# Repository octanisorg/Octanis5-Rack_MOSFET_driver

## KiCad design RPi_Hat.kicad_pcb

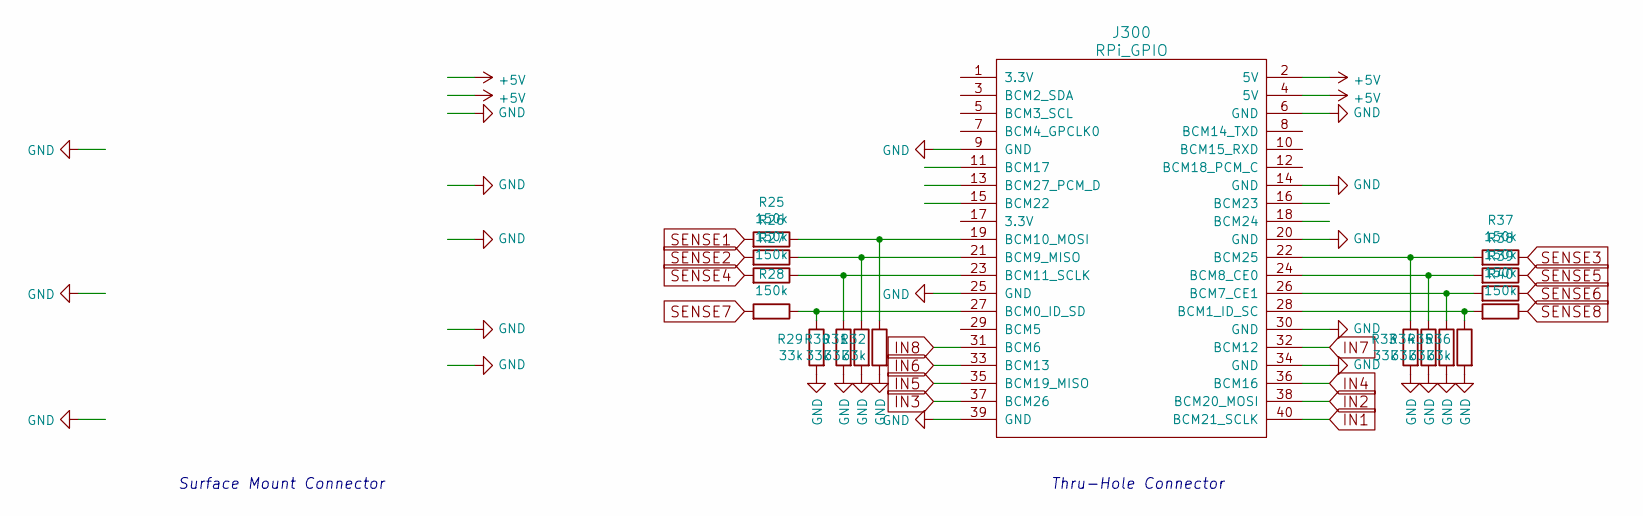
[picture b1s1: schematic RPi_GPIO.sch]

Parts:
J300: RPi_GPIO; Pin_Header_Straight_2x20; LCSC P/N C50982
R25, R26, R27, R28, R37, R38, R39, R40: 150k; R_0603; LCSC P/N C22807
R29, R30, R31, R32, R33, R34, R35, R36: 33k; R_0603; LCSC P/N C4216

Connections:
+5V: J300.2 (5V), J300.4 (5V); also elsewhere on the board
GND: J300.6 (GND), J300.9 (GND), J300.14 (GND), J300.20 (GND), J300.25 (GND), J300.30 (GND), J300.34 (GND), J300.39 (GND), R29.2, R30.2, R31.2, R32.2, R33.2, R34.2, R35.2, R36.2; also elsewhere on the board
IN1: J300.40 (BCM21_SCLK); also elsewhere on the board
IN2: J300.38 (BCM20_MOSI); also elsewhere on the board
IN3: J300.37 (BCM26); also elsewhere on the board
IN4: J300.36 (BCM16); also elsewhere on the board
IN5: J300.35 (BCM19_MISO); also elsewhere on the board
IN6: J300.33 (BCM13); also elsewhere on the board
IN7: J300.32 (BCM12); also elsewhere on the board
IN8: J300.31 (BCM6); also elsewhere on the board
unnamed: J300.19 (BCM10_MOSI), R25.1, R32.1
unnamed: J300.21 (BCM9_MISO), R26.1, R31.1
unnamed: J300.22 (BCM25), R33.1, R37.2
unnamed: J300.23 (BCM11_SCLK), R27.1, R30.1
unnamed: J300.24 (BCM8_CE0), R34.1, R38.2
unnamed: J300.26 (BCM7_CE1), R35.1, R39.2
unnamed: J300.27 (BCM0_ID_SD), R28.1, R29.1
unnamed: J300.28 (BCM1_ID_SC), R36.1, R40.2
SENSE1: R25.2; also elsewhere on the board
SENSE2: R26.2; also elsewhere on the board
SENSE3: R37.1; also elsewhere on the board
SENSE4: R27.2; also elsewhere on the board
SENSE5: R38.1; also elsewhere on the board
SENSE6: R39.1; also elsewhere on the board
SENSE7: R28.2; also elsewhere on the board
SENSE8: R40.1; also elsewhere on the board

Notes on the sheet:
Surface Mount Connector
Thru-Hole Connector

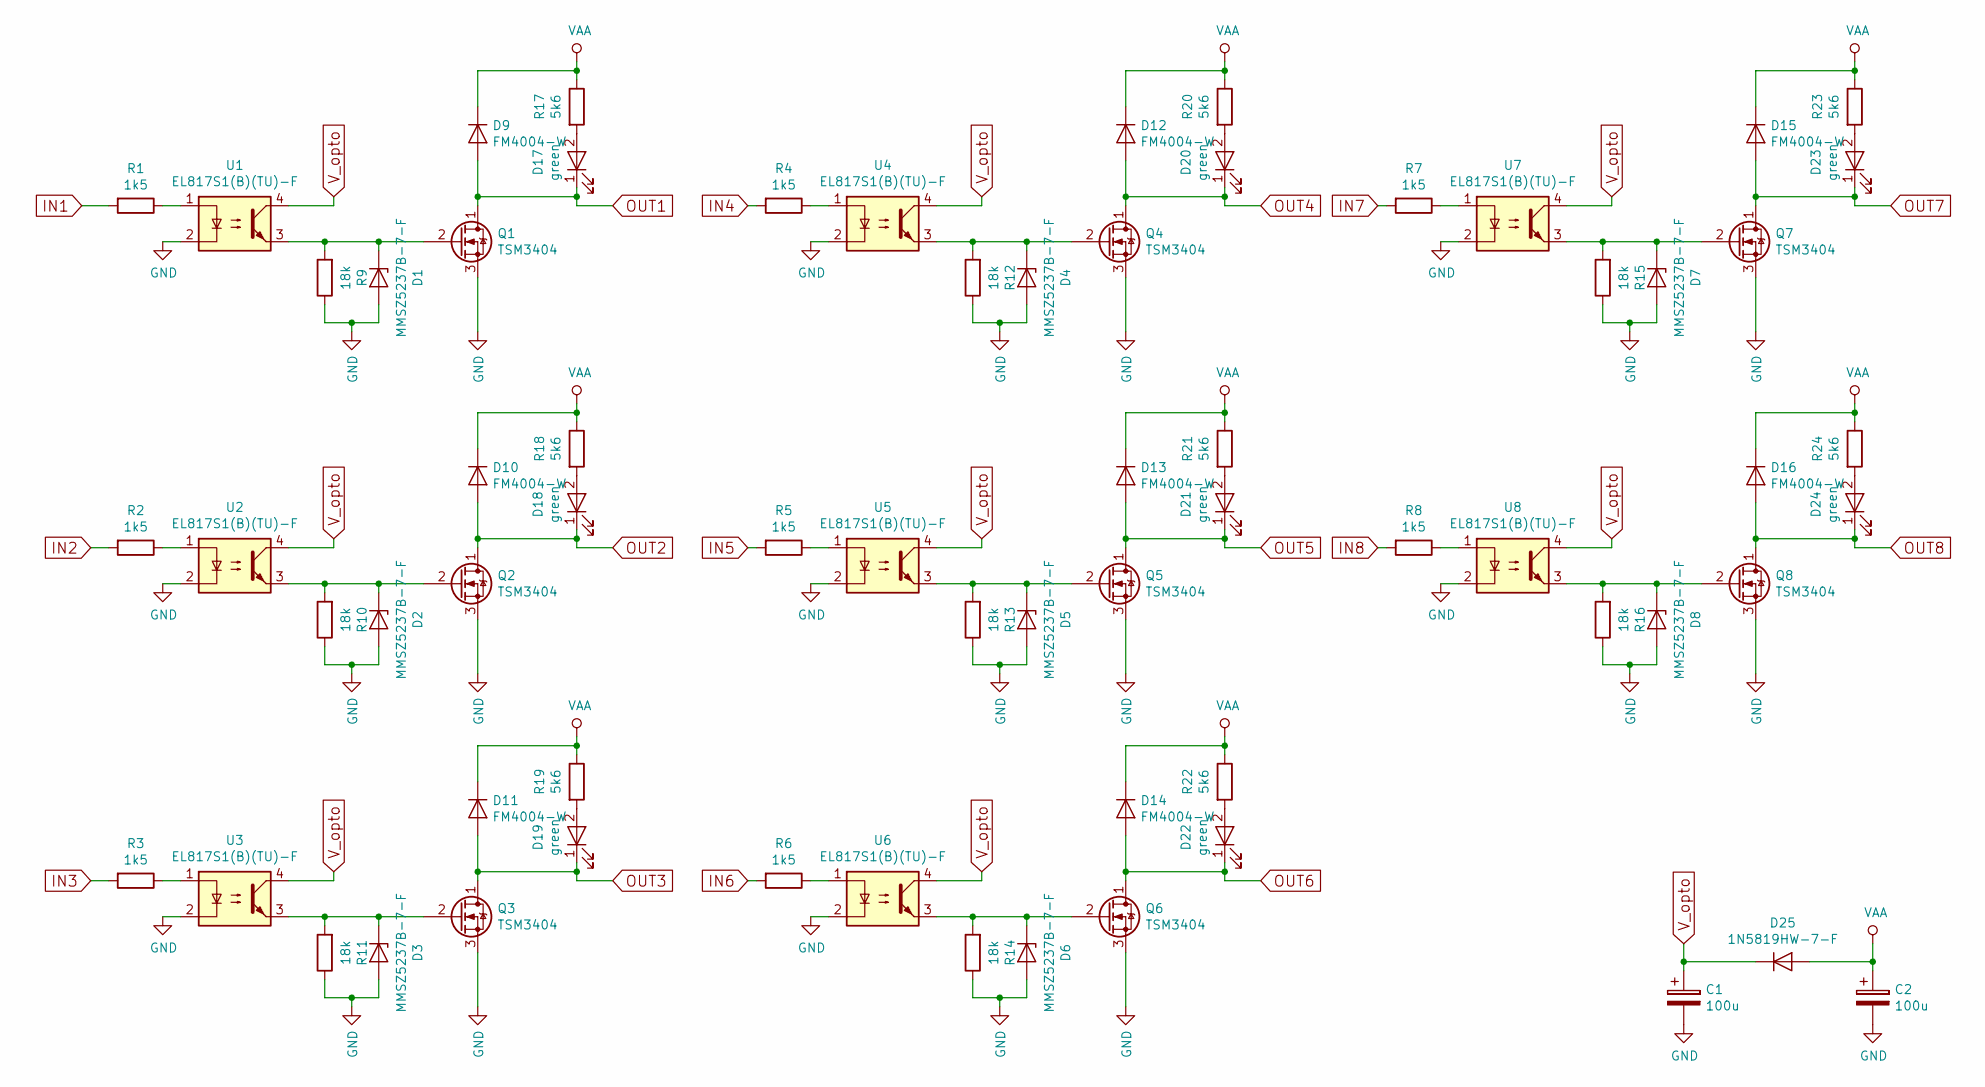
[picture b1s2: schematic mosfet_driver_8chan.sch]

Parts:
C1, C2: 100u; C_Radial_D8_L13_P3.8; LCSC P/N C45674
D1, D2, D3, D4, D5, D6, D7, D8: MMSZ5237B-7-F; SOD-123; LCSC P/N C65078
D9, D10, D11, D12, D13, D14, D15, D16: FM4004-W; SMB_Standard; LCSC P/N C122842
D17, D18, D19, D20, D21, D22, D23, D24: green; LED_0603; LCSC P/N C118334
D25: 1N5819HW-7-F; SOD-123; LCSC P/N C82544
Q1, Q2, Q3, Q4, Q5, Q6, Q7, Q8: TSM3404; SOT-23; LCSC P/N C71151
R1, R2, R3, R4, R5, R6, R7, R8: 1k5; R_0603; LCSC P/N C138275
R9, R10, R11, R12, R13, R14, R15, R16: 18k; R_0603; LCSC P/N C100821
R17, R18, R19, R20, R21, R22, R23, R24: 5k6; R_0603; LCSC P/N C101368
U1, U2, U3, U4, U5, U6, U7, U8: EL817S1(B)(TU)-F; EL817S1-B-TU-F; LCSC P/N C63268

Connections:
GND: C1.2, C2.2, D1.2 (A), D2.2 (A), D3.2 (A), D4.2 (A), D5.2 (A), D6.2 (A), D7.2 (A), D8.2 (A), Q1.3 (S), Q2.3 (S), Q3.3 (S), Q4.3 (S), Q5.3 (S), Q6.3 (S), Q7.3 (S), Q8.3 (S), R9.1, R10.1, R11.1, R12.1, R13.1, R14.1, R15.1, R16.1, U1.2, U2.2, U3.2, U4.2, U5.2, U6.2, U7.2, U8.2; also elsewhere on the board
IN1: R1.2; also elsewhere on the board
IN2: R2.2; also elsewhere on the board
IN3: R3.2; also elsewhere on the board
IN4: R4.2; also elsewhere on the board
IN5: R5.2; also elsewhere on the board
IN6: R6.2; also elsewhere on the board
IN7: R7.2; also elsewhere on the board
IN8: R8.2; also elsewhere on the board
unnamed: D1.1 (K), Q1.2 (G), R9.2, U1.3
unnamed: D2.1 (K), Q2.2 (G), R10.2, U2.3
unnamed: D3.1 (K), Q3.2 (G), R11.2, U3.3
unnamed: D4.1 (K), Q4.2 (G), R12.2, U4.3
unnamed: D5.1 (K), Q5.2 (G), R13.2, U5.3
unnamed: D6.1 (K), Q6.2 (G), R14.2, U6.3
unnamed: D7.1 (K), Q7.2 (G), R15.2, U7.3
unnamed: D8.1 (K), Q8.2 (G), R16.2, U8.3
unnamed: D17.2 (A), R17.2
unnamed: D18.2 (A), R18.2
unnamed: D19.2 (A), R19.2
unnamed: D20.2 (A), R20.2
unnamed: D21.2 (A), R21.2
unnamed: D22.2 (A), R22.2
unnamed: D23.2 (A), R23.2
unnamed: D24.2 (A), R24.2
unnamed: R1.1, U1.1
unnamed: R2.1, U2.1
unnamed: R3.1, U3.1
unnamed: R4.1, U4.1
unnamed: R5.1, U5.1
unnamed: R6.1, U6.1
unnamed: R7.1, U7.1
unnamed: R8.1, U8.1
OUT1: D9.2 (A), D17.1 (K), Q1.1 (D); also elsewhere on the board
OUT2: D10.2 (A), D18.1 (K), Q2.1 (D); also elsewhere on the board
OUT3: D11.2 (A), D19.1 (K), Q3.1 (D); also elsewhere on the board
OUT4: D12.2 (A), D20.1 (K), Q4.1 (D); also elsewhere on the board
OUT5: D13.2 (A), D21.1 (K), Q5.1 (D); also elsewhere on the board
OUT6: D14.2 (A), D22.1 (K), Q6.1 (D); also elsewhere on the board
OUT7: D15.2 (A), D23.1 (K), Q7.1 (D); also elsewhere on the board
OUT8: D16.2 (A), D24.1 (K), Q8.1 (D); also elsewhere on the board
VAA: C2.1, D9.1 (K), D10.1 (K), D11.1 (K), D12.1 (K), D13.1 (K), D14.1 (K), D15.1 (K), D16.1 (K), D25.2 (A), R17.1, R18.1, R19.1, R20.1, R21.1, R22.1, R23.1, R24.1; also elsewhere on the board
V_opto: C1.1, D25.1 (K), U1.4, U2.4, U3.4, U4.4, U5.4, U6.4, U7.4, U8.4

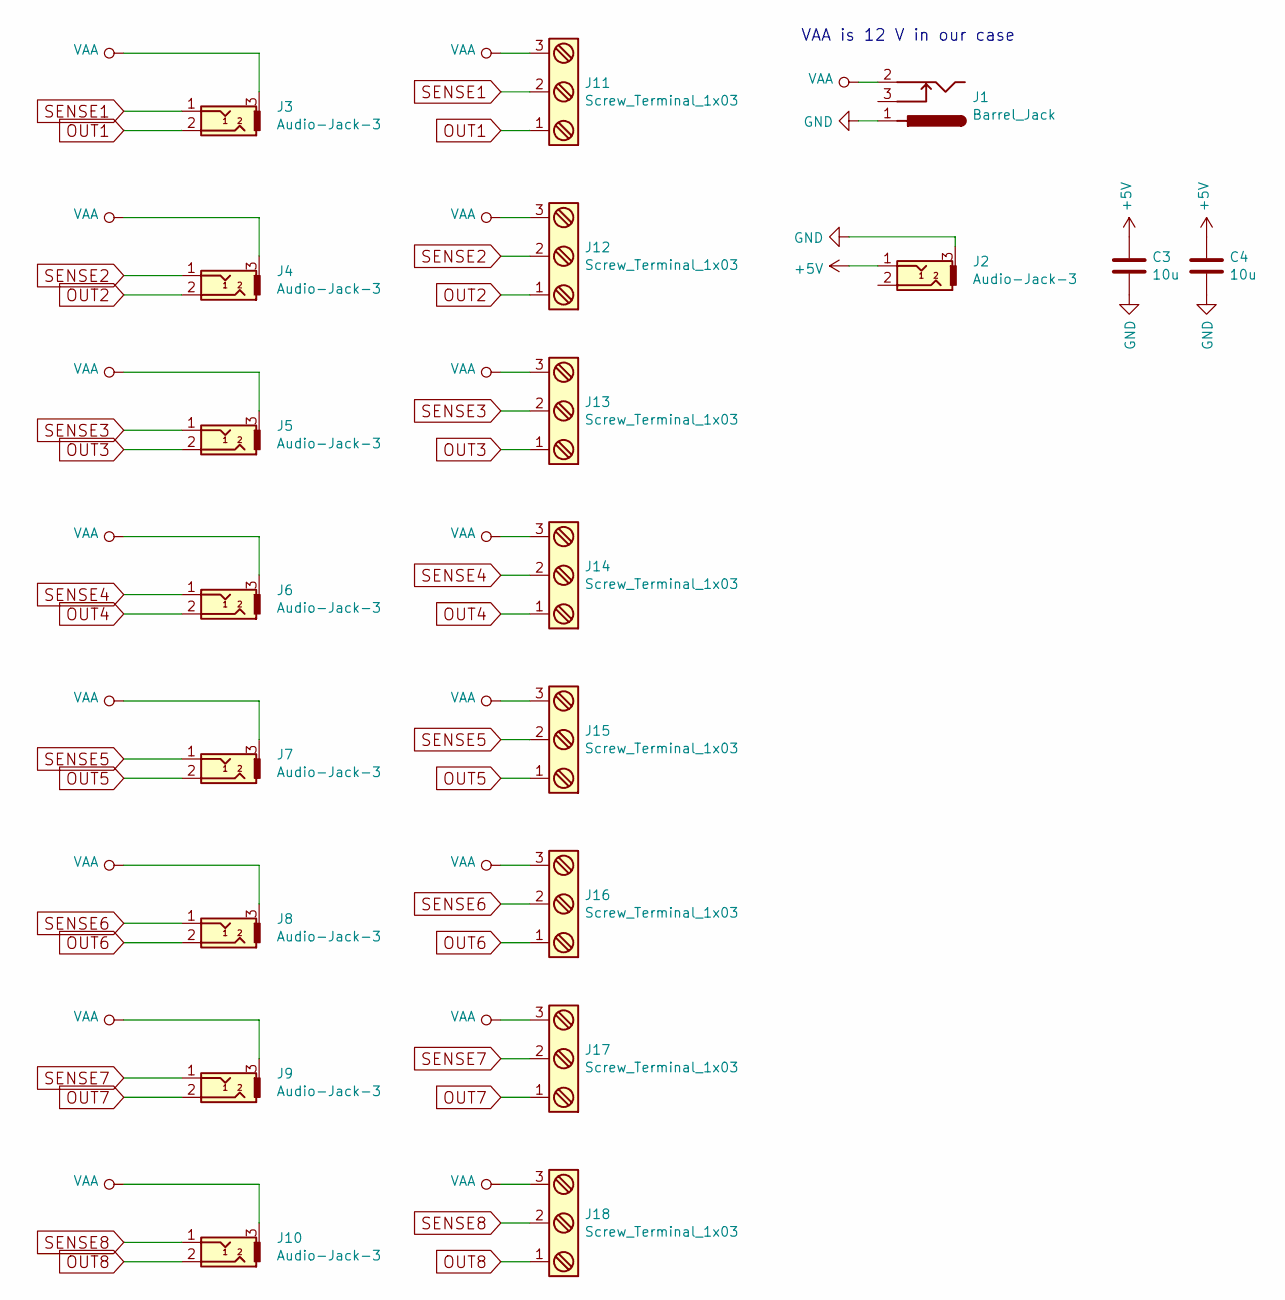
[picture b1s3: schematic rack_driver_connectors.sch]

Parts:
C3, C4: 10u; C_0805; LCSC P/N C123631
J1: Barrel_Jack; DC-005-20A; LCSC P/N C136744
J2, J3, J4, J5, J6, J7, J8, J9, J10: Audio-Jack-3; PJ-313D; LCSC P/N C95463
J11, J12, J13, J14, J15, J16, J17, J18: Screw_Terminal_1x03; JST_PH_B3B-PH-K_03x2.00mm_Straight; LCSC P/N C10400

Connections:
+5V: C3.1, C4.1, J2.1; also elsewhere on the board
GND: C3.2, C4.2, J1.1, J2.3; also elsewhere on the board
OUT1: J3.2, J11.1; also elsewhere on the board
OUT2: J4.2, J12.1; also elsewhere on the board
OUT3: J5.2, J13.1; also elsewhere on the board
OUT4: J6.2, J14.1; also elsewhere on the board
OUT5: J7.2, J15.1; also elsewhere on the board
OUT6: J8.2, J16.1; also elsewhere on the board
OUT7: J9.2, J17.1; also elsewhere on the board
OUT8: J10.2, J18.1; also elsewhere on the board
SENSE1: J3.1, J11.2; also elsewhere on the board
SENSE2: J4.1, J12.2; also elsewhere on the board
SENSE3: J5.1, J13.2; also elsewhere on the board
SENSE4: J6.1, J14.2; also elsewhere on the board
SENSE5: J7.1, J15.2; also elsewhere on the board
SENSE6: J8.1, J16.2; also elsewhere on the board
SENSE7: J9.1, J17.2; also elsewhere on the board
SENSE8: J10.1, J18.2; also elsewhere on the board
VAA: J1.2, J3.3, J4.3, J5.3, J6.3, J7.3, J8.3, J9.3, J10.3, J11.3, J12.3, J13.3, J14.3, J15.3, J16.3, J17.3, J18.3; also elsewhere on the board

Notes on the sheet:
VAA is 12 V in our case

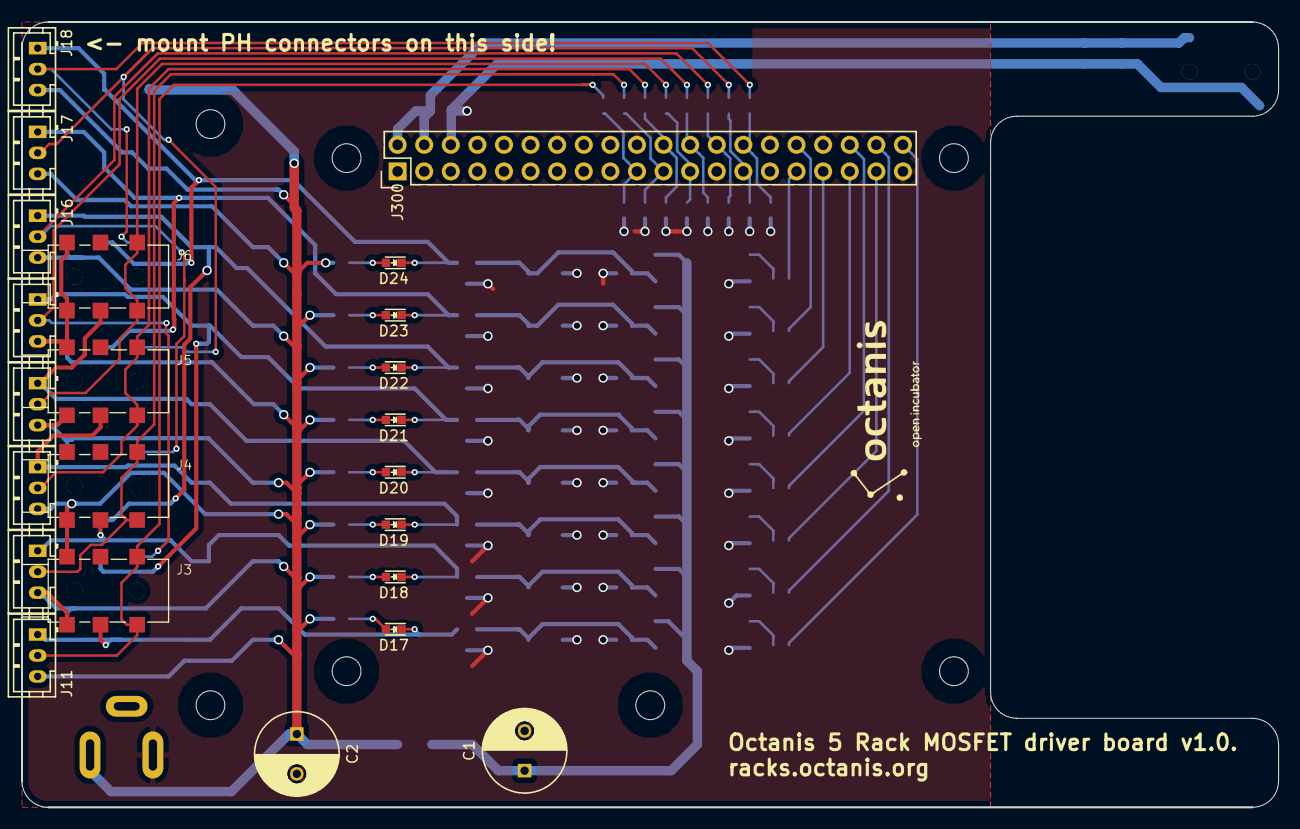
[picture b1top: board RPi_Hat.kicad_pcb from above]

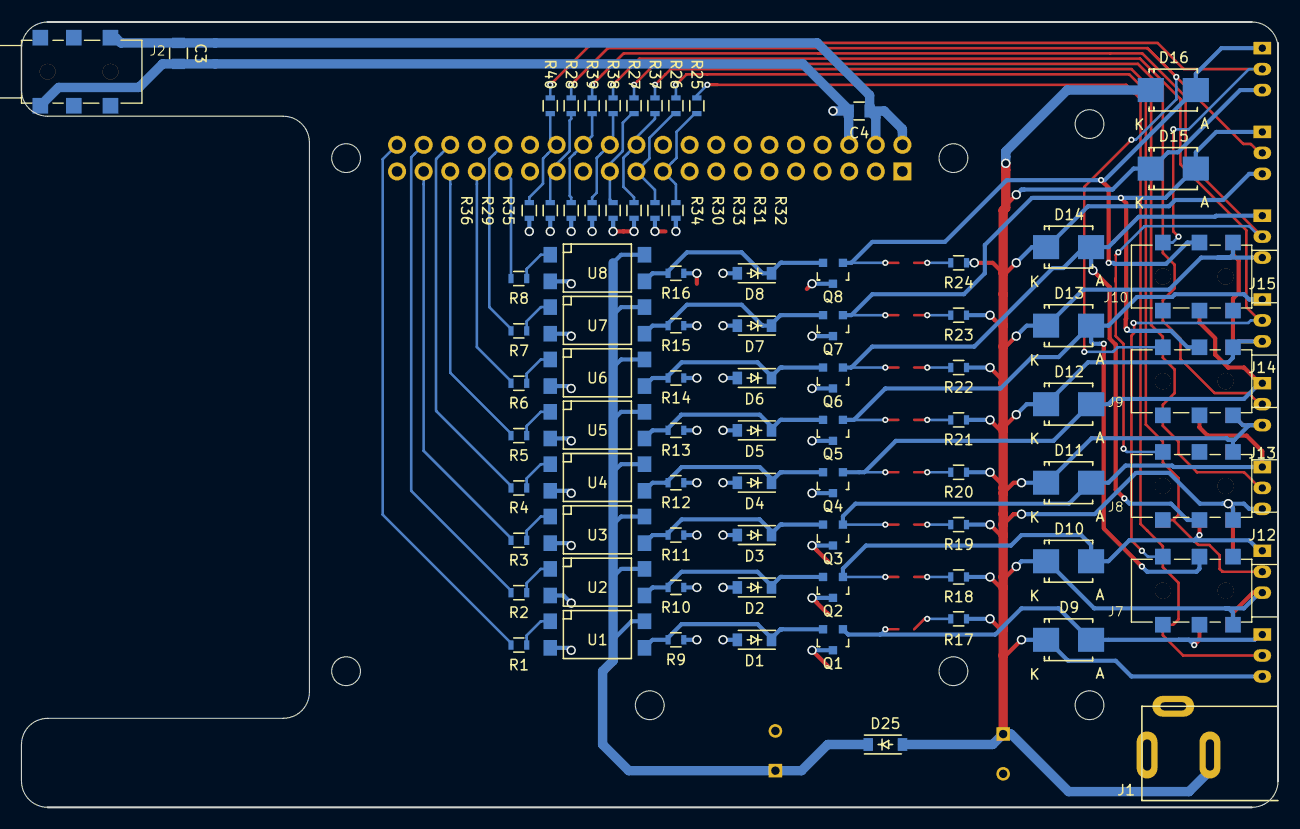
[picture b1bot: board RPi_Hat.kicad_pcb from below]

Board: 2 copper layers, 120.0 x 75.0 mm, 104 parts (81 on the bottom side), 60 nets.

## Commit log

2017-12-04 schematic done. PCB outline done. need to replace jack footprint
2017-12-04 halfway routed
2017-12-08 finished component placement
2017-12-08 finished routing
2017-12-09 final PCB as ordered
